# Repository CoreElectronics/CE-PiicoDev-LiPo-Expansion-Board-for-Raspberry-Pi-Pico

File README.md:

# PiicoDev® LiPo Expansion Board for Raspberry Pi Pico

The [PiicoDev® LiPo Expansion Board for Raspberry Pi Pico](https://core-electronics.com.au/catalog/product/view/sku/CE07693) is a great way to start experimenting with Raspberry Pi Pico/RP2040. Thanks to the onboard PiicoDev connector, you can quickly and easily connect to the PiicoDev family of sensor modules without soldering.

- Breaks out each Pico pin, with handy labels
- Take your project on the go with on-board LiPo battery charging.
- PiicoDev connector, compatible with Qwiic and STEMMA QT (3.3V only)
- Manufactured and [supported](https://core-electronics.com.au/contacts/) in Australia by Core Electronics

**Technical Details**

- Dimensions: 51x51mm
- M2.5 mounting holes
- Charge current: approx 220mA / 440mA (when Fast Charge jumper is soldered)
- PiicoDev connector: I2C0 (SCL:Pin 9, SDA:Pin 8)
- PiicoDev connector pinout:
  - 1 GND
  - 2 3.3V
  - 3 SDA
  - 4 SCL
- The I2C Bus presented at the PiicoDev connector contains series 120Ohm resistances to prevent destructive signal undershoot. Refer to the [schematic](Documents/schematic.pdf) for more information. To operate without these series resistors, users may connect directly to the GPIO instead.

# License
This project is open source - please review the LICENSE.md file for further licensing information.

If you have any technical questions, or concerns about licensing, please contact technical support on the [Core Electronics forums](https://forum.core-electronics.com.au/).

---
*\"PiicoDev" is a registered trademark of Core Electronics Pty Ltd*

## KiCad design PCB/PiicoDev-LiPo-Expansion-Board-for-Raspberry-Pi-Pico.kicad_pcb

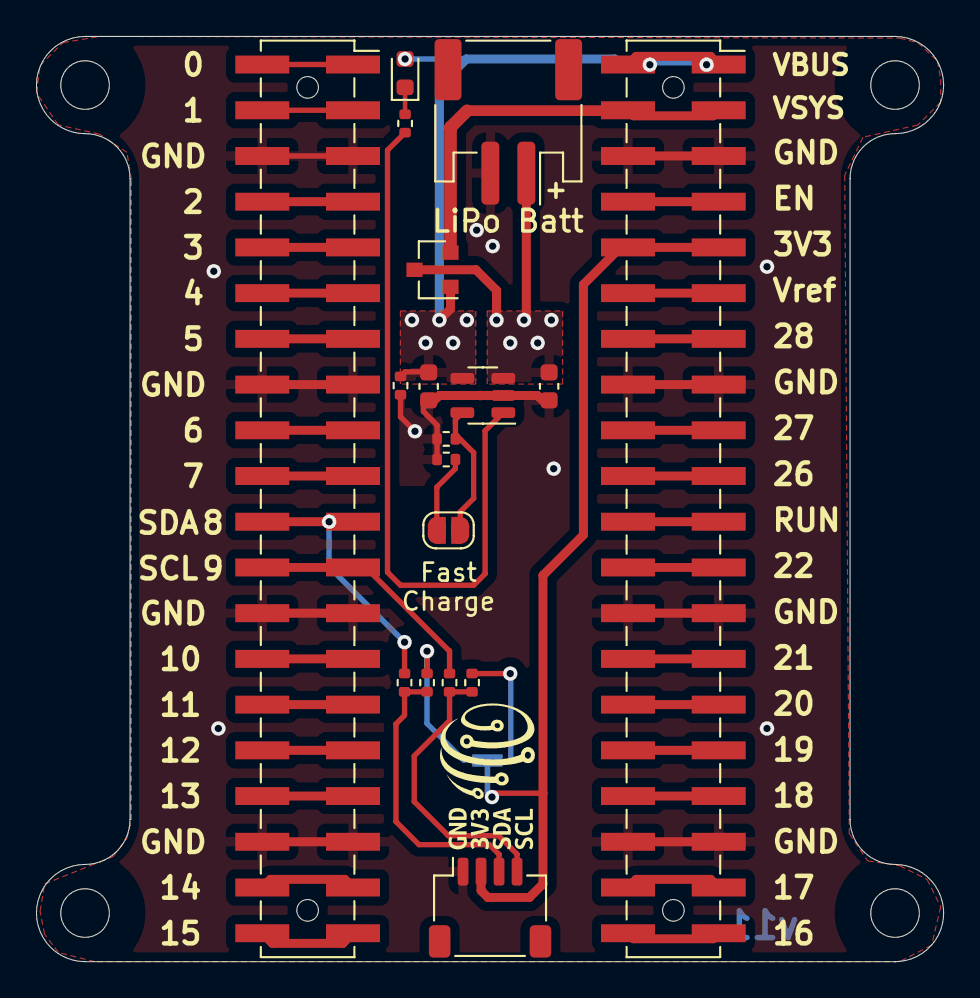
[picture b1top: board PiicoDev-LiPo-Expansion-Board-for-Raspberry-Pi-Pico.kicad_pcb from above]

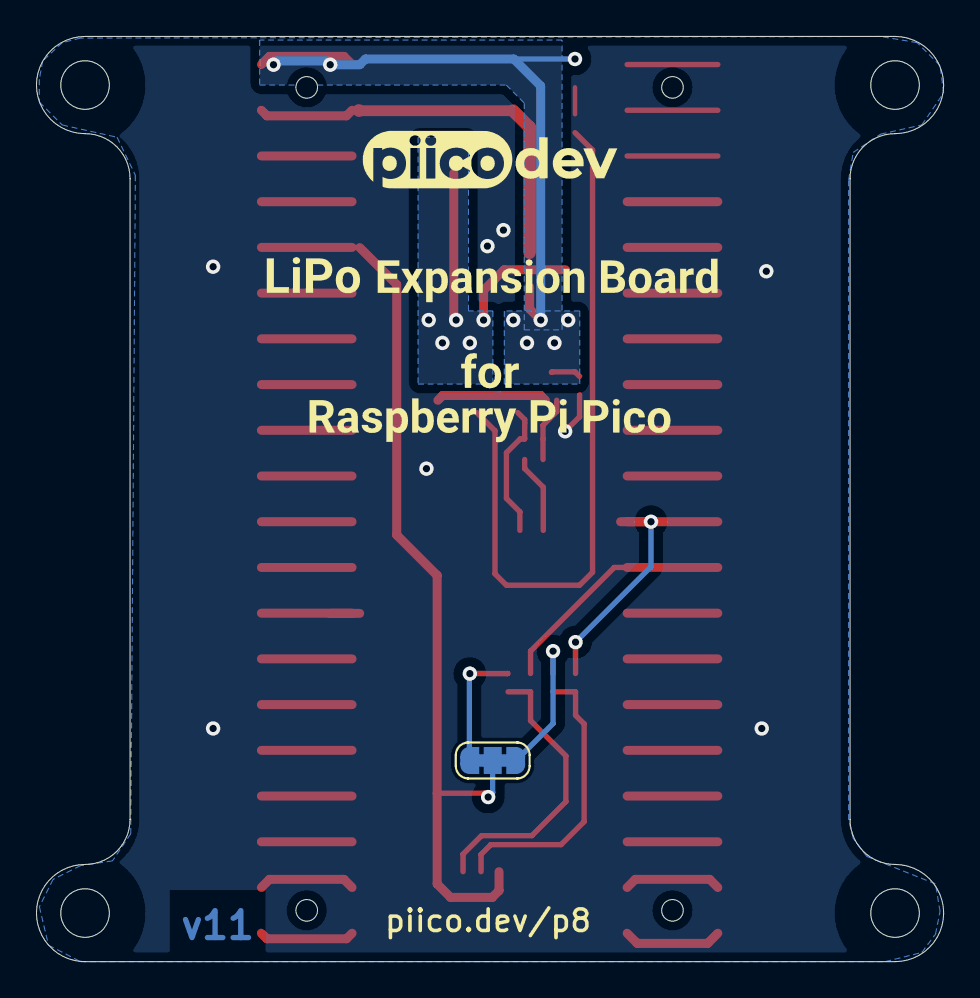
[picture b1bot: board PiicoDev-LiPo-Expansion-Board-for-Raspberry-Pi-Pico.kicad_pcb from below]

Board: 2 copper layers, 50.4 x 51.4 mm, 33 parts (6 on the bottom side), 42 nets.

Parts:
C1, C2: 10u; C_0603_1608Metric
D1: LED; LED_0603_1608Metric
G1: LOGO_CoreElectronics_made-with-love; CoreElectronics_logo_5mm
G2: LOGO_PiicoDev; piicodev_logo_14.2x3.4mm
H1, H2, H3, H4: MountingHole_2.7mm_M2.5
J1: PiicoDev; JST_SH_SM04B-SRSS-TB_1x04-1MP_P1.00mm_Horizontal
J2: JST PH; JST_PH_S2B-PH-SM4-TB_1x02-1MP_P2.00mm_Horizontal
J3, J4: PinSocket_2x20_P2.54mm_Vertical_SMD_With_Post
JP1: FAST_CHG; SolderJumper-2_P1.3mm_Open_RoundedPad1.0x1.5mm
JP2: I2C; SolderJumper-3_P1.3mm_Closed_RoundedPad1.0x1.5mm
Q1: DMG3415U-7; SOT-23
R1, R2, R3, R5, R6: 4k7; R_0402_1005Metric
R4: 100k; R_0402_1005Metric
R7, R8: 120R; R_0402_1005Metric
U1: MCP73832-2-OT; SOT-23-5
kibuzzard-62DE0FE6: G***; kibuzzard-62DE0FE6
kibuzzard-629D8D5D: G***; kibuzzard-629D8D5D
kibuzzard-629D8D6F: G***; kibuzzard-629D8D6F
kibuzzard-629D8D51: G***; kibuzzard-629D8D51
kibuzzard-629D8D64: G***; kibuzzard-629D8D64
kibuzzard-629D90AA: G***; kibuzzard-629D90AA
kibuzzard-629D909F: G***; kibuzzard-629D909F
kibuzzard-629D9090: G***; kibuzzard-629D9090

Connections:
+3V3: J1.2, J4.9, J4.10, JP2.2
/I2C0_SCL: J3.23, J3.24, R8.1
/I2C0_SDA: J3.21, J3.22, R7.1
/VSYS: J4.3, J4.4, Q1.2
GND: C1.2, C2.2, J1.1, J2.2, J3.5, J3.6, J3.15, J3.16, J3.25, J3.26, J3.35, J3.36, J4.5, J4.6, J4.15, J4.16, J4.25, J4.26, J4.35, J4.36, R1.2, R3.2, R4.2, U1.2
unnamed: D1.1, R2.2
unnamed: J1.3, R5.2, R7.2
unnamed: J1.4, R6.2, R8.2
unnamed: J3.1, J3.2
unnamed: J3.3, J3.4
unnamed: J3.7, J3.8
unnamed: J3.9, J3.10
unnamed: J3.11, J3.12
unnamed: J3.13, J3.14
unnamed: J3.17, J3.18
unnamed: J3.19, J3.20
unnamed: J3.27, J3.28
unnamed: J3.29, J3.30
unnamed: J3.31, J3.32
unnamed: J3.33, J3.34
unnamed: J3.37, J3.38
unnamed: J3.39, J3.40
unnamed: J4.7, J4.8
unnamed: J4.11, J4.12
unnamed: J4.13, J4.14
unnamed: J4.17, J4.18
unnamed: J4.19, J4.20
unnamed: J4.21, J4.22
unnamed: J4.23, J4.24
unnamed: J4.27, J4.28
unnamed: J4.29, J4.30
unnamed: J4.31, J4.32
unnamed: J4.33, J4.34
unnamed: J4.37, J4.38
unnamed: J4.39, J4.40
unnamed: JP1.1, R3.1
unnamed: JP1.2, R1.1, U1.5
unnamed: JP2.1, R6.1
unnamed: JP2.3, R5.1
unnamed: R2.1, U1.1
VBAT: C1.1, J2.1, Q1.3, U1.3
VBUS: C2.1, D1.2, J4.1, J4.2, Q1.1, R4.1, U1.4

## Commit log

2021-04-25 Add datasheet for the charge IC
    Add datasheet for the charge IC
2021-10-28 Update links and silk text
2021-10-29 Add 120R to SCL & SDA. Improve silk screen.
2021-12-30 Change LED Resistor from 1k to 4.7k
2022-02-24 Update schematic pdf to v11
2022-07-11 Update project to KiCad v6
2022-07-11 Rename project to '... LiPo Expansion...'
2022-07-11 update schematic title block
2022-07-25 update artwork for 'LiPo' expansion
